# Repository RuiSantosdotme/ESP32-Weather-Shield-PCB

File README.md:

# Build an All-in-One ESP32 Weather Station Shield

In this project I’ll show you how you can build an all-in-one ESP32 weather station shield and display the sensor readings on a web server. The web server displays data from all the sensors and automatically updates the readings every ten seconds, without the need to refresh the web page.

You can watch the video tutorial and demonstration here: https://youtu.be/m5cS21AAhZo

For the complete step-by-step instructions, visit: https://randomnerdtutorials.com/build-an-all-in-one-esp32-weather-station-shield/

How to browse the GitHub repository:
- [Web server code (for Arduino IDE)](https://raw.githubusercontent.com/RuiSantosdotme/ESP32-Weather-Shield-PCB/master/Code/ESP32_Weather_Station_Shield/ESP32_Weather_Station_Shield.ino)
- [HTML page](https://raw.githubusercontent.com/RuiSantosdotme/ESP32-Weather-Shield-PCB/master/Code/index.html)
- [Schematic diagram](https://github.com/RuiSantosdotme/ESP32-Weather-Shield-PCB/tree/master/Images)
- [Gerber files](https://github.com/RuiSantosdotme/ESP32-Weather-Shield-PCB/raw/master/KiCad_PCB_ESP32_Shield/GERBERS/ESP32_Shield_Gerbers.zip)
- [KiCad project to edit the PCB](https://github.com/RuiSantosdotme/ESP32-Weather-Shield-PCB/tree/master/KiCad_PCB_ESP32_Shield)
- [Click here to download all the files](https://github.com/RuiSantosdotme/ESP32-Weather-Shield-PCB/archive/master.zip)

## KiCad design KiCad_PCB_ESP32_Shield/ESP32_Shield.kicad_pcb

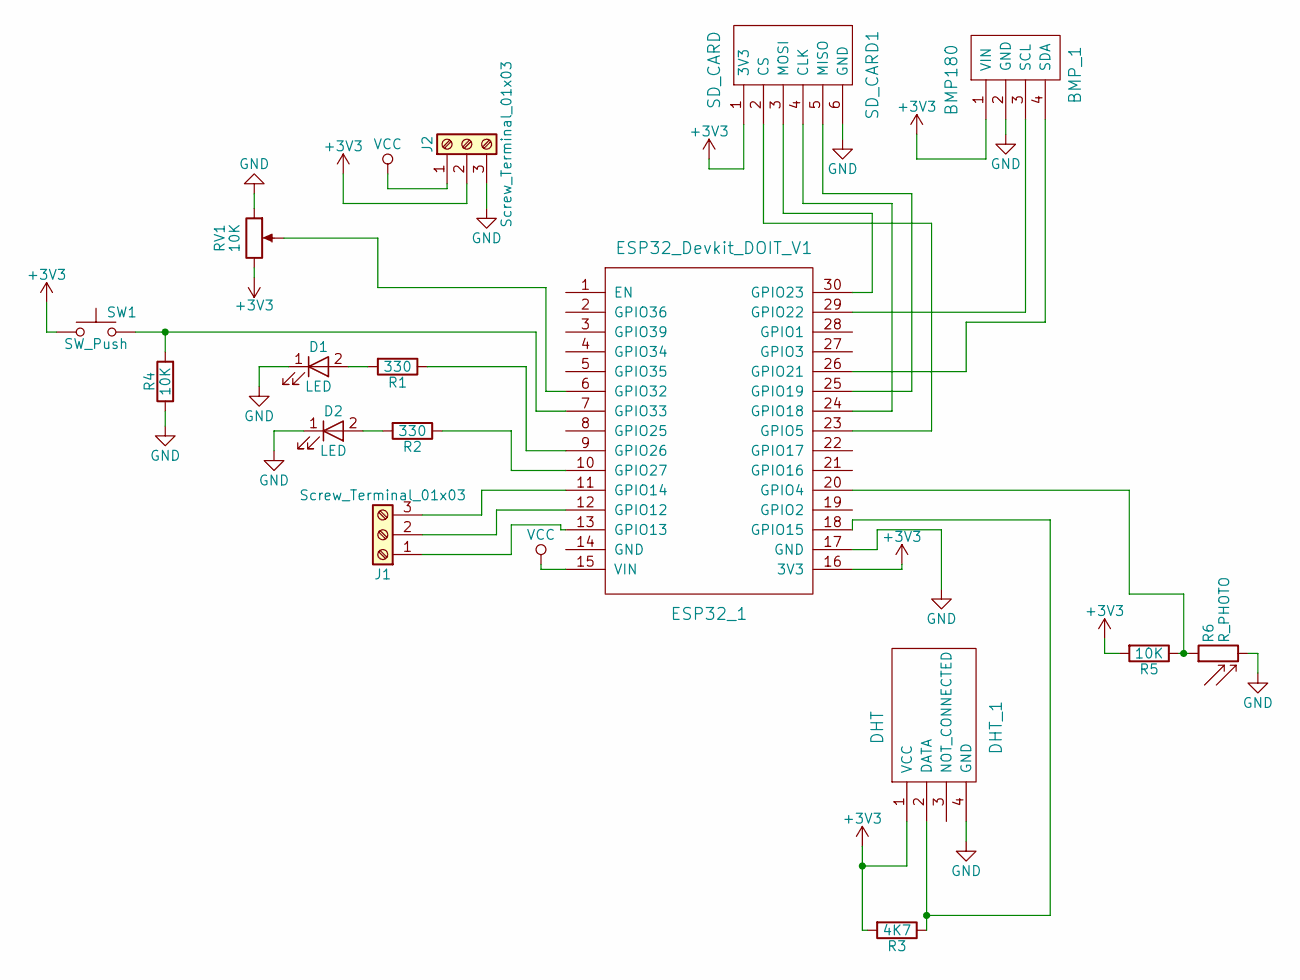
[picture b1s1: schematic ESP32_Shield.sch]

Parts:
BMP_1: BMP180
D1, D2: LED; LED_1206_HandSoldering
DHT_1: DHT
ESP32_1: ESP32_Devkit_DOIT_V1
J1: Screw_Terminal_01x03; TerminalBlock_5mm_Pins
J2: Screw_Terminal_01x03; TerminalBlock_5mm
R1, R2: 330; R_0805_HandSoldering
R3: 4K7; R_0805_HandSoldering
R4, R5: 10K; R_0805_HandSoldering
R6: R_PHOTO; R_Axial_DIN0207_L6.3mm_D2.5mm_P7.62mm_Horizontal
RV1: 10K; Potentiometer_Trimmer_ACP_CA6v_Horizontal
SD_CARD1: SD_CARD
SW1: SW_Push; SW_PUSH_6mmx6mm

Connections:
+3V3: BMP_1.1 (VIN), DHT_1.1 (VCC), ESP32_1.16 (3V3), J2.2, R3.2, R5.2, RV1.3, SD_CARD1.1 (3V3), SW1.1
GND: BMP_1.2 (GND), D1.1 (K), D2.1 (K), DHT_1.4 (GND), ESP32_1.17 (GND), J2.3, R4.1, R6.2, RV1.1, SD_CARD1.6 (GND)
unnamed: BMP_1.3 (SCL), ESP32_1.29 (GPIO22)
unnamed: BMP_1.4 (SDA), ESP32_1.26 (GPIO21)
unnamed: D1.2 (A), R1.2
unnamed: D2.2 (A), R2.2
unnamed: DHT_1.2 (DATA), ESP32_1.18 (GPIO15), R3.1
unnamed: ESP32_1.6 (GPIO32), RV1.2
unnamed: ESP32_1.7 (GPIO33), R4.2, SW1.2
unnamed: ESP32_1.9 (GPIO26), R1.1
unnamed: ESP32_1.10 (GPIO27), R2.1
unnamed: ESP32_1.11 (GPIO14), J1.3
unnamed: ESP32_1.12 (GPIO12), J1.2
unnamed: ESP32_1.13 (GPIO13), J1.1
unnamed: ESP32_1.20 (GPIO4), R5.1, R6.1
unnamed: ESP32_1.23 (GPIO5), SD_CARD1.2 (CS)
unnamed: ESP32_1.24 (GPIO18), SD_CARD1.4 (CLK)
unnamed: ESP32_1.25 (GPIO19), SD_CARD1.5 (MISO)
unnamed: ESP32_1.30 (GPIO23), SD_CARD1.3 (MOSI)
VCC: ESP32_1.15 (VIN), J2.1

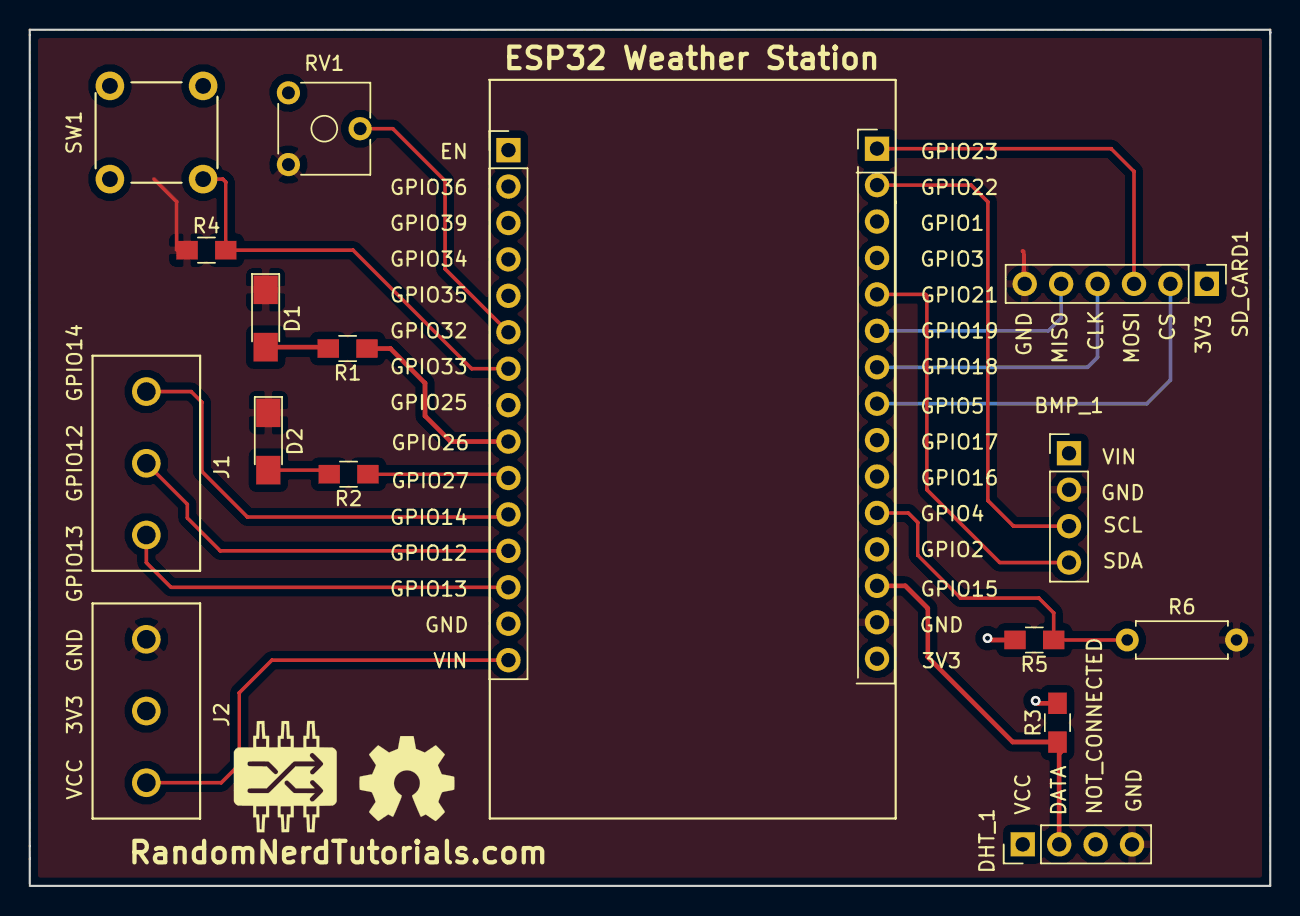
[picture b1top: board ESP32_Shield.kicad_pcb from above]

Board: 2 copper layers, 86.5 x 59.7 mm, 16 parts (0 on the bottom side), 20 nets.

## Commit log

2018-02-06 KiCad Project
2018-02-06 Project circuit and Images
2018-02-06 Arduino Code for ESP32 and HTML page
